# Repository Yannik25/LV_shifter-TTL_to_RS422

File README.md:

# LV_shifter-TTL_to_RS422

Top view:<br />
<br />
Bottom view:<br />
<br />
## Configuration

### Simple 3.3V to 5V Levelshifter:

### Digital LED over long cable with RS422:
Sender: From ESP (3.3V pin) -> Levelshift to 5V -> Translate to RS422 -> send out.<br />
Receiver: receive RS422 -> translate back -> control 5V digital LED.

Sender solder config       |  Receiver solder config
:-------------------------:|:-------------------------:
   |

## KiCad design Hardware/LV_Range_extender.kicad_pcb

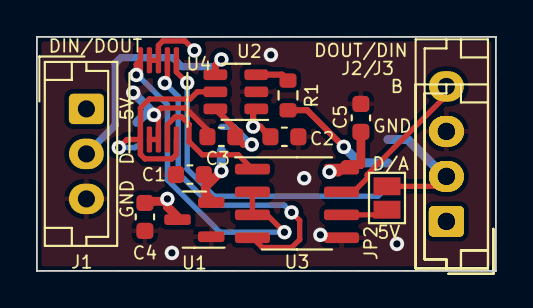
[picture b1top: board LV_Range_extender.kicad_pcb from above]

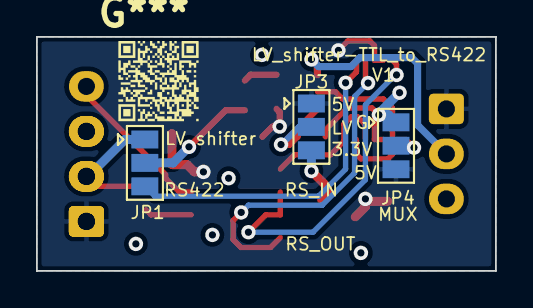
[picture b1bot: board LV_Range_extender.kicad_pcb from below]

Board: 2 copper layers, 25.5 x 13.0 mm, 17 parts (3 on the bottom side), 15 nets.

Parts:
C1, C2, C3, C4, C5: 0.1uF; C_0603_1608Metric
J1, J2: Conn_01x03_Female; JST_EH_B3B-EH-A_1x03_P2.50mm_Vertical
J3: Conn_01x04_Female; JST_EH_B4B-EH-A_1x04_P2.50mm_Vertical
JP1, JP3, JP4: SolderJumper_3_Open; SolderJumper-3_P1.3mm_Open_Pad1.0x1.5mm
JP2: SolderJumper_2_Open; SolderJumper-2_P1.3mm_Open_Pad1.0x1.5mm
R1: 150; R_0603_1608Metric
U1: ME6211A33M3G-N; SOT-23
U2: SN74LVC1T45DBV; SOT-23-6
U3: SN75176AD; SOIC-8_3.9x4.9mm_P1.27mm
U4: TS5A23159DGS; VSSOP-10_3x3mm_P0.5mm

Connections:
+3V3: C1.2, JP3.3 (B), U1.2 (VO)
+5V: C2.1, C4.2, C5.2, J1.1, J2.1, J3.1, JP3.1 (A), JP4.3 (B), U1.3 (VI), U2.1 (VCCA), U3.8 (VCC), U4.8 (VCC), U4.9
B: J3.4, U3.7 (B)
DOUT/A: J2.2, J3.2, JP1.1 (A), JP2.1 (A)
Driver: U3.4 (D), U4.7
GND: C1.1, C2.2, C3.1, C4.1, C5.1, J1.3, J2.3, J3.3, JP4.1 (A), U1.1 (GND), U2.2 (GND), U3.5 (GND), U4.2, U4.3 (GND)
LV_A: JP1.2 (C), R1.1
LV_B: J1.2, U2.4 (B)
MUX: JP4.2 (C), U2.5 (DIR), U4.1, U4.5
unnamed: C3.2, JP3.2 (C), U2.6 (VCCB)
unnamed: R1.2, U2.3 (A)
unnamed: JP2.2 (B), U3.6 (A)
RS: JP1.3 (B), U4.6
RS_Enable: U3.2 (~RE), U3.3 (DE), U4.10
Receiver: U3.1 (R), U4.4

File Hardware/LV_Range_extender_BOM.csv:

Comment,Designator,Footprint,LCSC
0.1uF,C1 C2 C3 C4 C5,Capacitor_SMD:C_0603_1608Metric
150,R1,Resistor_SMD:R_0603_1608Metric
ME6211A33M3G-N,U1,Package_TO_SOT_SMD:SOT-23
SN74LVC1T45DBV,U2,Package_TO_SOT_SMD:SOT-23-6
SN75176AD,U3,Package_SO:SOIC-8_3.9x4.9mm_P1.27mm
TS5A23159DGS,U4,Package_SO:VSSOP-10_3x3mm_P0.5mm

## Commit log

2022-02-01 initial Release
2022-02-01 add multiplexer
2022-02-02 update multiplexing
2022-02-03 Add ordered version V1
2022-05-25 add images for solder config
2024-12-25 Update LV_Range_extender-top-pos.csv
    Correct placement orientation of ICs
